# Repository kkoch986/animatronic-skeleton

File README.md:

# Animatronic Skeletons v4

This branch represents the latest code to support my v2.x skeleton boards
these boards, unlike their predecessors run on ESP8266 and are controlled
completely via websockets.

TODO: fill this out more including the protocol details, and other important stuff

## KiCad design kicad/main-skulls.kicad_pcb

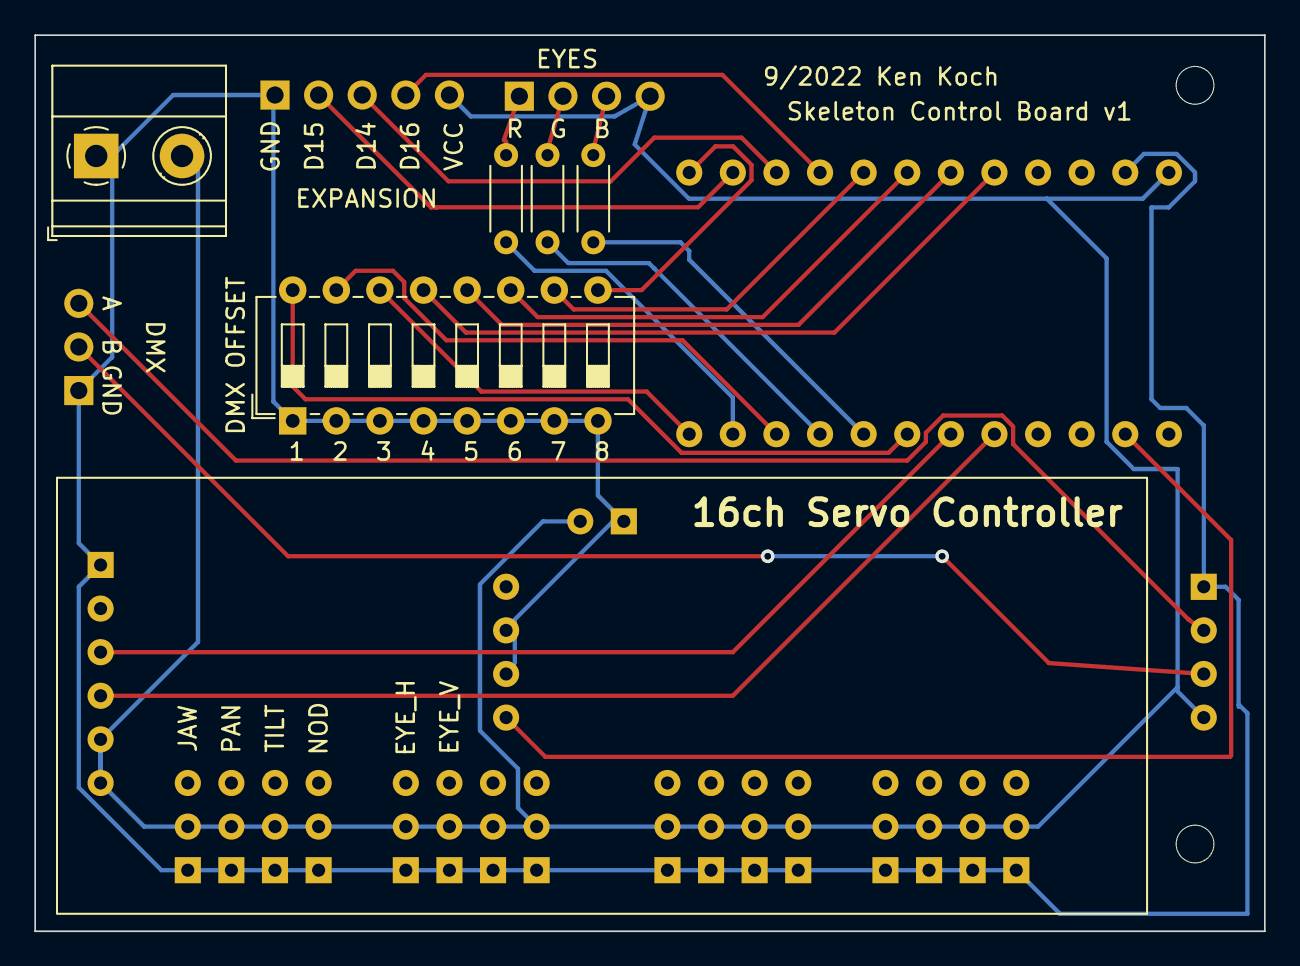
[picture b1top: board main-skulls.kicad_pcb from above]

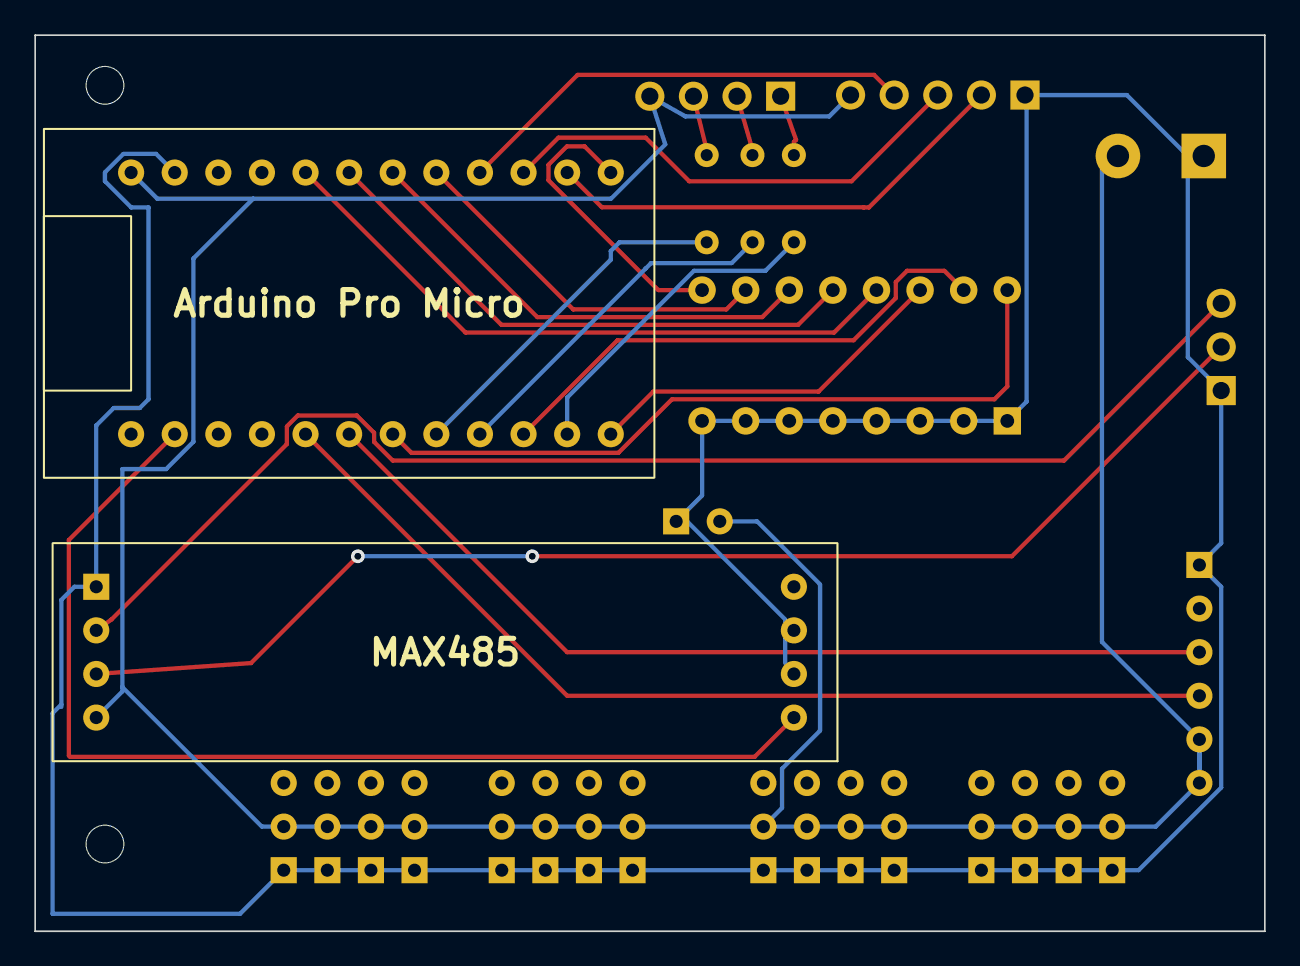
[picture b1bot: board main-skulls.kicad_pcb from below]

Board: 2 copper layers, 71.6 x 52.2 mm, 11 parts (2 on the bottom side), 24 nets.

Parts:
D2: Right Eye; PinHeader_1x04_P2.54mm_Horizontal
J2: DMX OUT (female); PinHeader_1x03_P2.54mm_Horizontal
J3: Expansion Slots; PinHeader_1x05_P2.54mm_Horizontal
J4: Power Input; TerminalBlock_Phoenix_MKDS-1,5-2_1x02_P5.00mm_Horizontal
R1, R2, R3: R; R_Axial_DIN0204_L3.6mm_D1.6mm_P5.08mm_Horizontal
SW1: DMX Channel Offset Selection; SW_DIP_SPSTx08_Slide_6.7x21.88mm_W7.62mm_P2.54mm_LowProfile
U1: MAX485E; MAX485
U2: ProMicro; arduino pro micro
U3: 16ch Servo Controller; Adafruit 16ch Servo controller

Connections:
/485RO: U1.1 (RO), U2.2 (RX)
/ADDR_1: SW1.16, U2.7 (D4)
/ADDR_2: SW1.15, U2.10 (E6)
/ADDR_3: SW1.14, U2.12 (B5)
/ADDR_4: SW1.13, U2.20 (F4)
/ADDR_5: SW1.12, U2.19 (F5)
/ADDR_6: SW1.11, U2.18 (F6)
/ADDR_7: SW1.10, U2.17 (F7)
/ADDR_8: SW1.9, U2.13 (B6)
/EYE_B: R1.2, U2.11 (B4)
/EYE_G: R2.2, U2.9 (D7)
/EYE_R: R3.2, U2.8 (C6)
/SERVO_SCL: U2.6 (SCL), U3.23 (SCL)
/SERVO_SDA: U2.5 (SDA), U3.24 (SDA)
GND: J2.1, J3.1, J4.1, SW1.1, SW1.2, SW1.3, SW1.4, SW1.5, SW1.6, SW1.7, SW1.8, U1.2 (~RE), U1.3 (DE), U1.5 (GND), U2.23 (GND), U3.25 (VDD)
unnamed: D2.1 (RK), R1.1
unnamed: D2.2 (GK), R2.1
unnamed: D2.3 (BK), R3.1
unnamed: J2.2, U1.7 (B)
unnamed: J2.3, U1.6 (A)
unnamed: J3.2, U2.14 (B2)
unnamed: J3.3, U2.15 (B3)
unnamed: J3.4, U2.16 (B1)
VCC: D2.4 (A), J3.5, J4.2, U1.8 (VCC), U2.24 (RAW), U3.11 (VSS)

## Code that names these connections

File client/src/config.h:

#pragma once

// Networking configuration
#define OTA_PORT 8266

// Status LED Pins
#define STATUS_GREEN 16
#define STATUS_BLUE 13
#define STATUS_RED 12

// The pins to read the control address from
// this is purely an application level address
// not to be confused with the I2C address for controlling
// the PWM chip
#define ADDR_0 10
#define ADDR_1 9
#define ADDR_2 5
#define ADDR_3 4

#define RESET_BUTTON 0

// The total number of available servos
#define SERVO_COUNT 16
#define SERVO_MAX_LABEL_SIZE 8

// ENABLED, MIN, MAX, IDLE, SMOOTH, CURRENT, TARGET, ARRIVED, LABELSIZE, LABEL
// (MAX_LABEL_SIZE bytes)
#define SERVO_DUMP_BYTES_PER_SERVO (9 + SERVO_MAX_LABEL_SIZE)

// This will get used as the hostname for the device so it needs to
// conform to the valid character set of a DNS name
// also its loaded into a 32 byte buffer so keep it below 29 characters
// to allow room for up to 2 digits of address
#define CONTROL_ADDR_FMT "skeleton-%d"

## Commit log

2021-09-22 initial code, very wip
2021-09-22 document the par lights
2021-09-23 fix up the readme
2021-09-25 update makefile baud rate for logs
2021-10-06 trying out renard again...
2021-10-27 more updates
2023-05-09 add schematics
2024-04-27 initial code for v2.1 boards
    this is a websockets-based approach. i think i am going to switch gears
    and replace it with MQTT but wanted to keep this code around in case i
    want to go back to it
2024-07-26 a whole bunch of new stuff
    idk why i waiting this long to commit it all...
2024-08-27 remove smoothing from firmware
    was doing it mostly to debug some issues but i think i can manage it
    better in chataigne so i dont think the firmware needs the extra
    complexity.
2024-09-06 fixup! remove smoothing from firmware
2024-09-12 fixup! fixup! remove smoothing from firmware
2024-09-26 add a bunch more features
    starting to doubt the viability of the websockets for the live
    performances so next commits might try to move back to DMX
2024-10-07 more tweaks and fixes
2025-07-05 add telnet command for movement
    also adds websocket address to telnet websocket info
2025-09-06 more firmware updates
